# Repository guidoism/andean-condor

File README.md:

# Andean Condor

48 key monoblock split keyboard

## Characteristics

- 3x6 core + 6 key thumb cluster per hand
- Pro-micro MCU footprint (note: it's right-side-up which apparently goes against the current trend)
- Nice!View headers (untested)

## Inspiration 

- Kyria -- A huge inpsiration, the thumb cluster in particular is taken directly from the Kyria
- Absolem -- Monoblock split and angles taken from Absolem

## Changes in version 3

- Move diodes to sit next to their switches to save space and use SMT to reduce size and holes
- Move reset switch away from usb plug
- Move Nice!View to its standard location just below the Nice!Nano
- Screw holes for MCU plate cover and seperate MCU plate cover with optional place for Nice!View
- Second PCB attached to top PCB to hide pointy through hole component stuff
- Holes in the PCB in a few places for magnets to hole keyboard inside case without screws
- Place to attach larger battery so it's not flopping around
- Place to connect battery to PCB rather than directly to Nice!Nano
- Place for 8x1 neopixels to indicate stuff? Maybe on plate cover?
- Place 7-segment display? Maybe on plate cover?
- Maybe plate cover has legs to break out pins?

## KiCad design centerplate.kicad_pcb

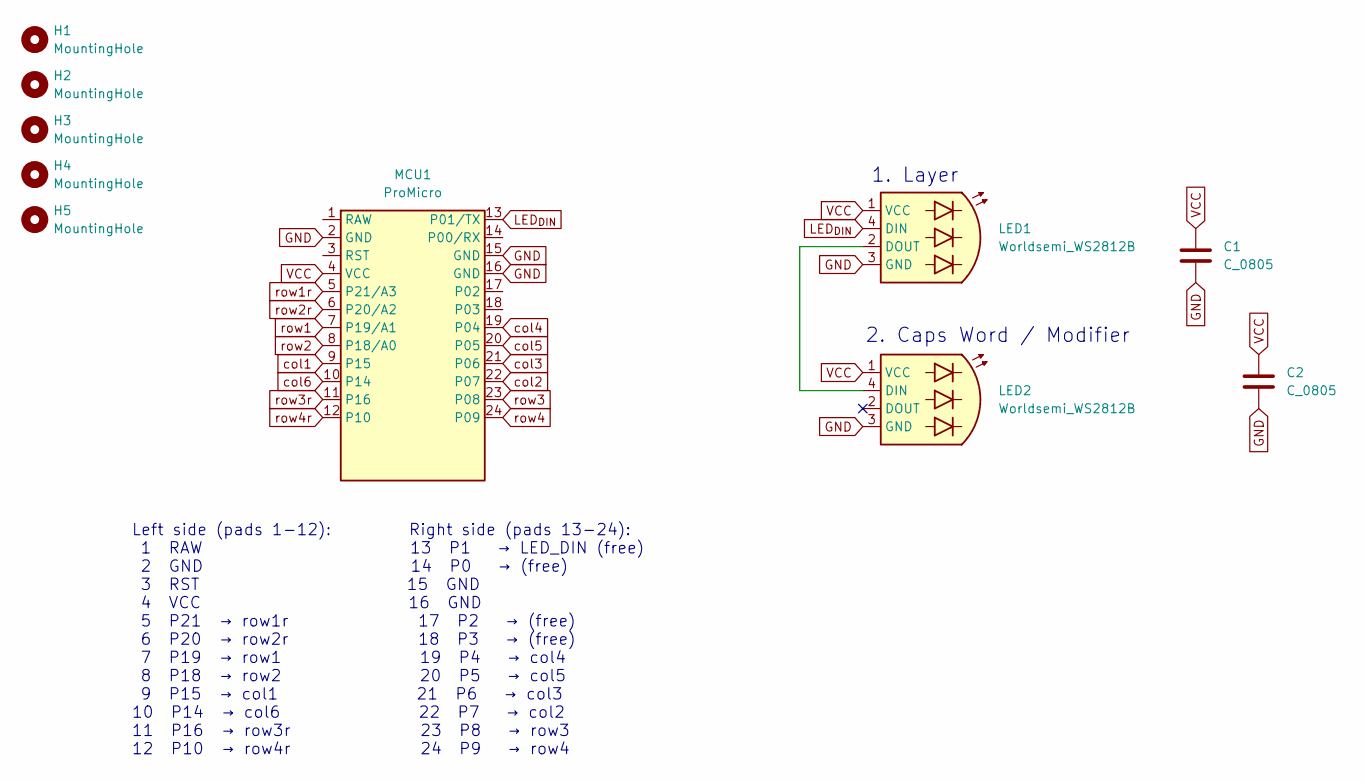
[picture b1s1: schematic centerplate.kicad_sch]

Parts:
C1, C2: C_0805; C_0805_2012Metric
H1, H2, H3, H4, H5: MountingHole; M2_HOLE_v3
LED1, LED2: Worldsemi_WS2812B; LED_WS2812B_PLCC4_5.0x5.0mm_P3.2mm
MCU1: ProMicro

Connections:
GND: C1.2, C2.2, LED1.3 (GND), LED2.3 (GND), MCU1.2 (GND), MCU1.15 (GND), MCU1.16 (GND)
LED_{DIN}: LED1.4 (DIN), MCU1.13 (P01/TX)
unnamed: LED1.2 (DOUT), LED2.4 (DIN)
VCC: C1.1, C2.1, LED1.1 (VCC), LED2.1 (VCC), MCU1.4 (VCC)
col1: MCU1.9 (P15)
col2: MCU1.22 (P07)
col3: MCU1.21 (P06)
col4: MCU1.19 (P04)
col5: MCU1.20 (P05)
col6: MCU1.10 (P14)
row1: MCU1.7 (P19/A1)
row1r: MCU1.5 (P21/A3)
row2: MCU1.8 (P18/A0)
row2r: MCU1.6 (P20/A2)
row3: MCU1.23 (P08)
row3r: MCU1.11 (P16)
row4: MCU1.24 (P09)
row4r: MCU1.12 (P10)

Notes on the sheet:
Left side (pads 1-12): Right side (pads 13-24): 1 RAW 13 P1 → LED_DIN (free) 2 GND 14 P0 → (free) 3 RST 15 GND 4 VCC 16 GND 5 P21 → row1r 17 P2 → (free) 6 P20 → row2r 18 P3 → (free) 7 P19 → row1 19 P4 → col4 8 P18 → row2 20 P5 → col5 9 P15 → col1 21 P6 → col3 10 P14 → col6 22 P7 → col2 11 P16 → row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
2. Caps Word / Modifier
1. Layer

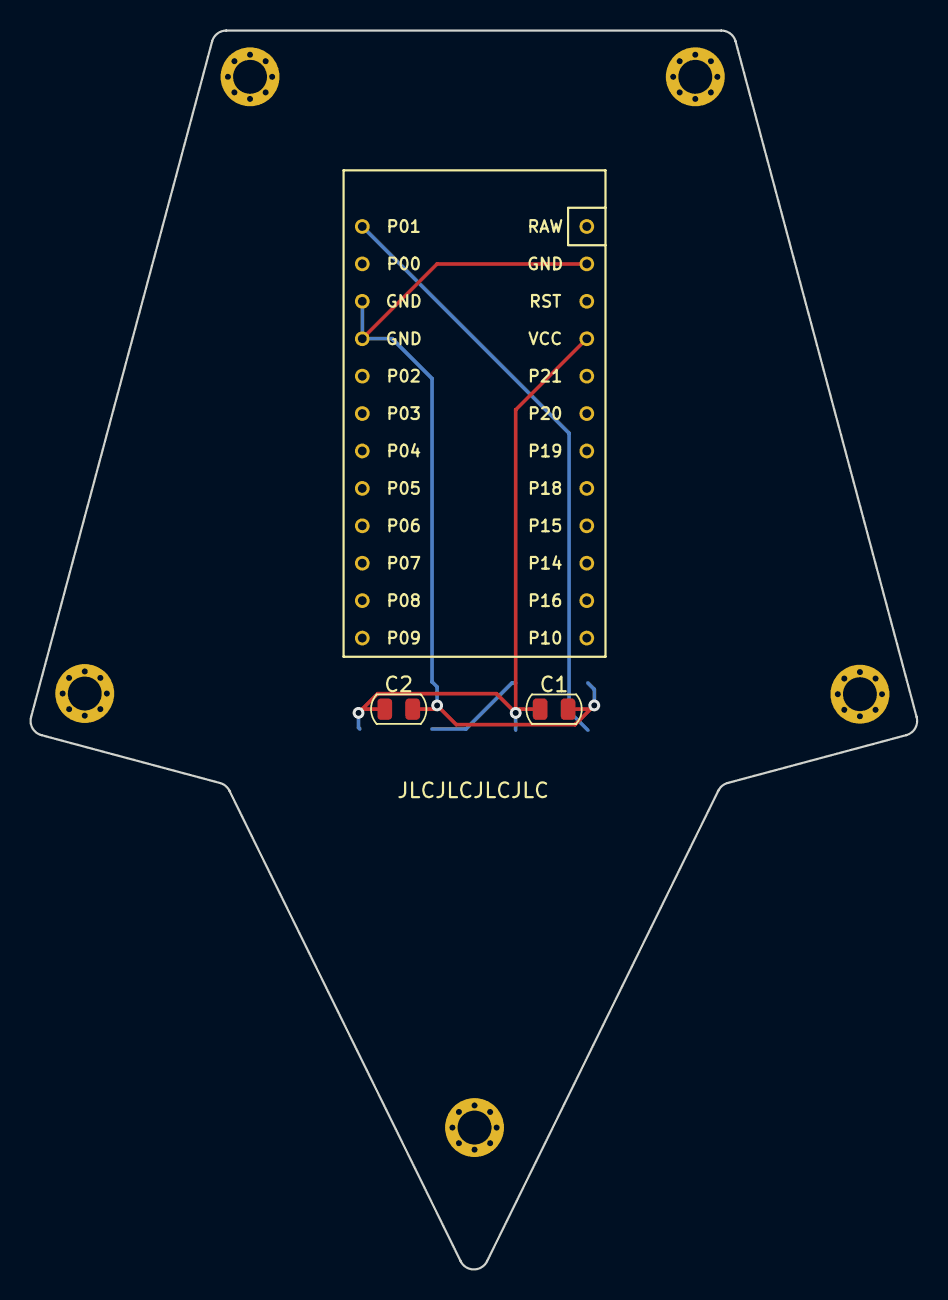
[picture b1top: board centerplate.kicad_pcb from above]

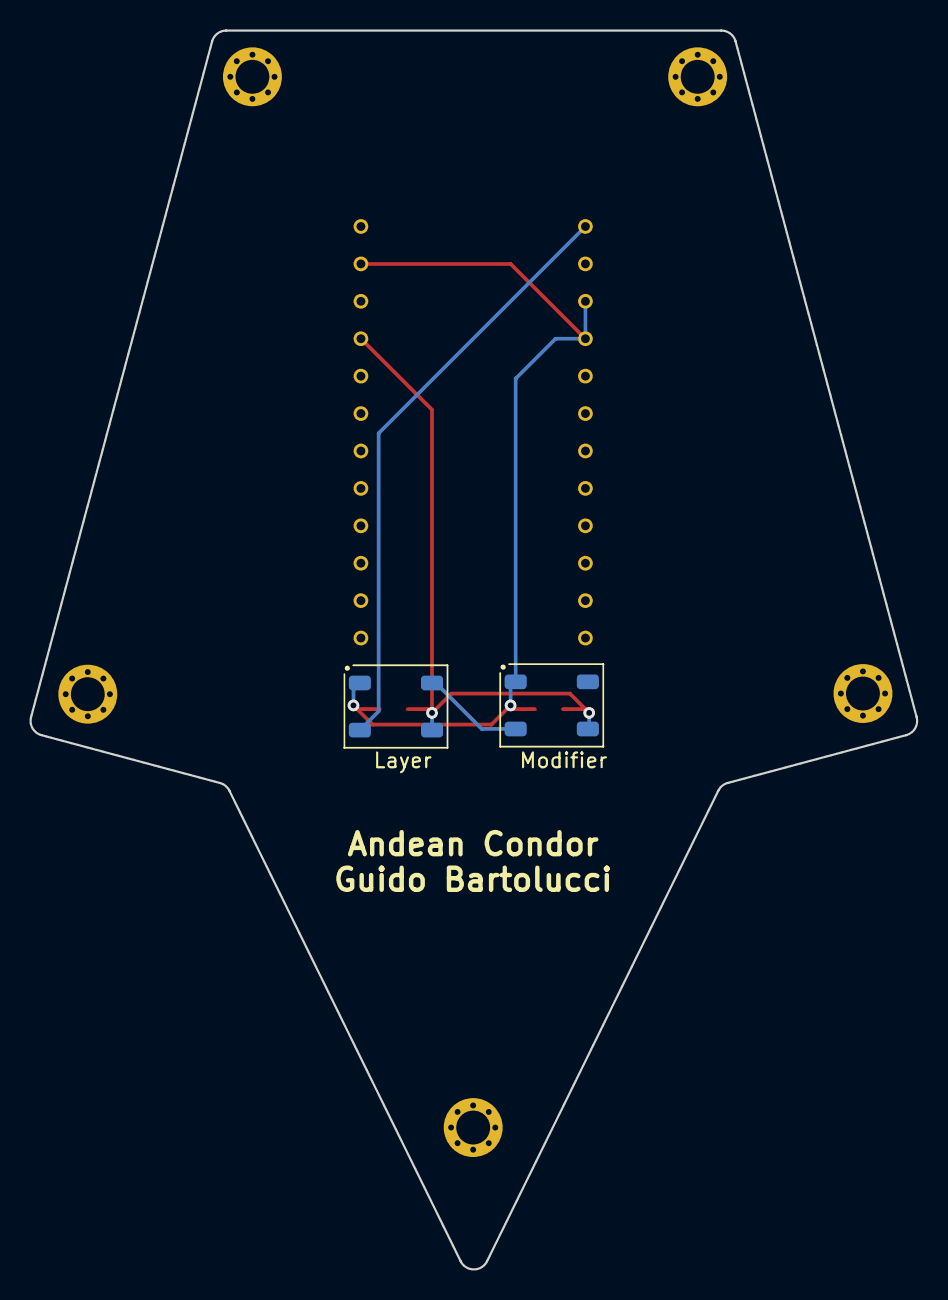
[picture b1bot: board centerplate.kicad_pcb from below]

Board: 2 copper layers, 60.2 x 84.1 mm, 10 parts (2 on the bottom side), 4 nets.

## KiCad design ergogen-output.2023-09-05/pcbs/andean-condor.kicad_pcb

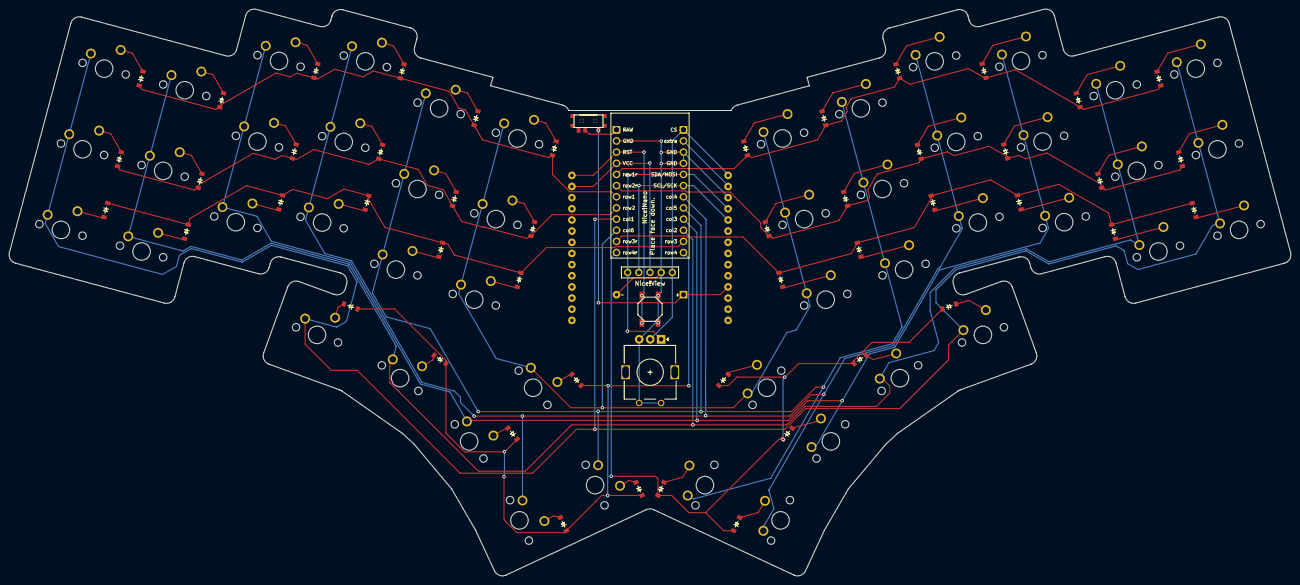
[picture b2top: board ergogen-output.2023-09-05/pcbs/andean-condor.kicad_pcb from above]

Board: 2 copper layers, 291.8 x 129.0 mm, 101 parts (0 on the bottom side), 69 nets.

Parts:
B1: SW_TACT_ALPS_SKQGABE010
D1, D2, D3, D4, D5, D6, D7, D8, D9, D10, D11, D12, D13, D14, D15, D16, D17, D18, D19, D20, D21, D22, D23, D24, D25, D26, D27, D28, D29, D30, D31, D32, D33, D34, D35, D36, D37, D38, D39, D40, D41, D42, D43, D44, D45, D46, D47, D48: ComboDiode
MCU1: ProMicro
Nice!View1: niceview_headers
ROT1: rotary_encoder
S1, S2, S3, S4, S5, S6, S7, S8, S9, S10, S11, S12, S13, S14, S15, S16, S17, S18, S19, S20, S21, S22, S23, S24, S25, S26, S27, S28, S29, S30, S31, S32, S33, S34, S35, S36, S37, S38, S39, S40, S41, S42, S43, S44, S45, S46, S47, S48: MX
T1: SPDT_C128955

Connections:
CS: MCU1.13, Nice!View1.1, ROT1.C
GND: B1.1, MCU1.2, MCU1.15, MCU1.16, Nice!View1.1, ROT1.1, ROT1.2, ROT1.B
RAW: MCU1.1, T1.2
RST: B1.2, MCU1.3
SCL: MCU1.18, Nice!View1.3
SDA: MCU1.17, Nice!View1.4, ROT1.A
VCC: MCU1.4, Nice!View1.2
col1: MCU1.9, S1.2, S2.2, S3.2, S19.2, S25.2, S26.2, S27.2, S43.2
col2: MCU1.22, S4.2, S5.2, S6.2, S20.2, S28.2, S29.2, S30.2, S44.2
col3: MCU1.21, S7.2, S8.2, S9.2, S21.2, S31.2, S32.2, S33.2, S45.2
col4: MCU1.19, S10.2, S11.2, S12.2, S23.2, S34.2, S35.2, S36.2, S47.2
col5: MCU1.20, S13.2, S14.2, S15.2, S24.2, S37.2, S38.2, S39.2, S48.2
col6: MCU1.10, S16.2, S17.2, S18.2, S22.2, S40.2, S41.2, S42.2, S46.2
far_thumb: D41.2, S23.1
far_top: D42.2, S24.1
farpinky_bottom: D13.2, S1.1
farpinky_home: D1.2, S2.1
farpinky_top: D2.2, S3.1
home_thumb: D39.2, S21.1
home_top: D40.2, S22.1
index_bottom: D17.2, S13.1
index_home: D9.2, S14.1
index_top: D10.2, S15.1
inner_bottom: D18.2, S16.1
inner_home: D11.2, S17.1
inner_top: D12.2, S18.1
middle_bottom: D16.2, S10.1
middle_home: D7.2, S11.1
middle_top: D8.2, S12.1
mirror_far_thumb: D47.2, S47.1
mirror_far_top: D48.2, S48.1
mirror_farpinky_bottom: D31.2, S25.1
mirror_farpinky_home: D19.2, S26.1
mirror_farpinky_top: D20.2, S27.1
mirror_home_thumb: D45.2, S45.1
mirror_home_top: D46.2, S46.1
mirror_index_bottom: D35.2, S37.1
mirror_index_home: D27.2, S38.1
mirror_index_top: D28.2, S39.1
mirror_inner_bottom: D36.2, S40.1
mirror_inner_home: D29.2, S41.1
mirror_inner_top: D30.2, S42.1
mirror_middle_bottom: D34.2, S34.1
mirror_middle_home: D25.2, S35.1
mirror_middle_top: D26.2, S36.1
mirror_near_thumb: D44.2, S44.1
mirror_pinky_bottom: D32.2, S28.1
mirror_pinky_home: D21.2, S29.1
mirror_pinky_top: D22.2, S30.1
mirror_ring_bottom: D33.2, S31.1
mirror_ring_home: D23.2, S32.1
mirror_ring_top: D24.2, S33.1
mirror_tucky_thumb: D43.2, S43.1
near_thumb: D38.2, S20.1
pinky_bottom: D14.2, S4.1
pinky_home: D3.2, S5.1
pinky_top: D4.2, S6.1
ring_bottom: D15.2, S7.1
ring_home: D5.2, S8.1
ring_top: D6.2, S9.1
row1: D2.1, D4.1, D6.1, D8.1, D10.1, D12.1, MCU1.7
row1r: D20.1, D22.1, D24.1, D26.1, D28.1, D30.1, MCU1.5
row2: D1.1, D3.1, D5.1, D7.1, D9.1, D11.1, MCU1.8
row2r: D19.1, D21.1, D23.1, D25.1, D27.1, D29.1, MCU1.6
row3: D13.1, D14.1, D15.1, D16.1, D17.1, D18.1, MCU1.23
row3r: D31.1, D32.1, D33.1, D34.1, D35.1, D36.1, MCU1.11
row4: D37.1, D38.1, D39.1, D40.1, D41.1, D42.1, MCU1.24
row4r: D43.1, D44.1, D45.1, D46.1, D47.1, D48.1, MCU1.12
tucky_thumb: D37.2, S19.1

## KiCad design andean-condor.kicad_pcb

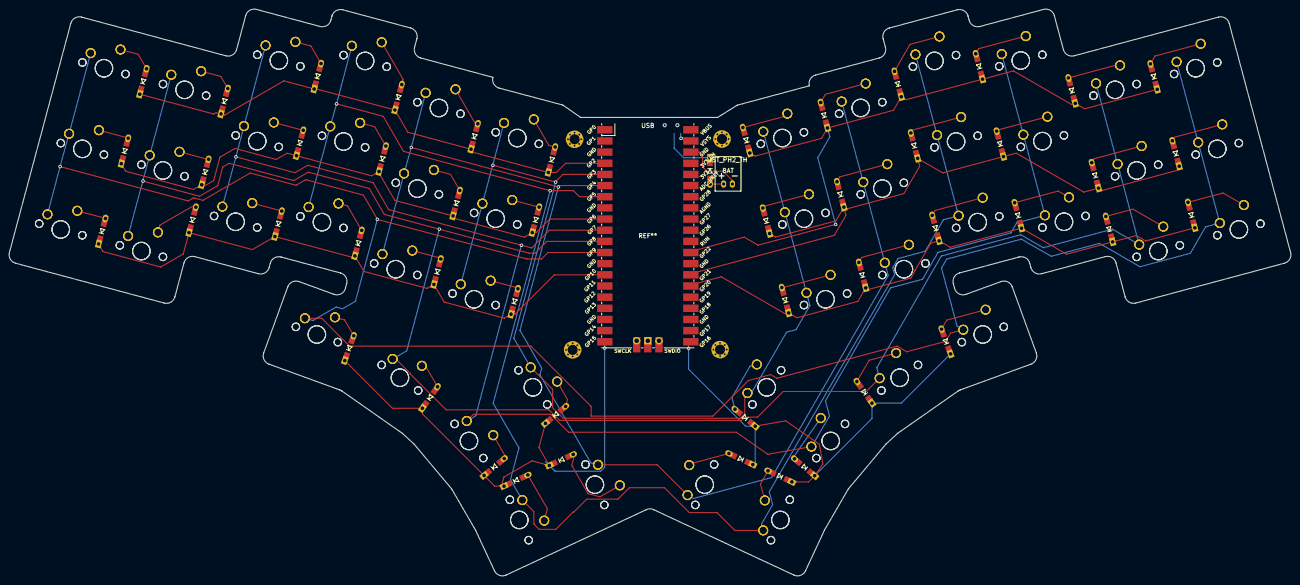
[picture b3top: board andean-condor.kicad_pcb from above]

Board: 2 copper layers, 291.8 x 129.0 mm, 151 parts (1 on the bottom side), 62 nets.

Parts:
D33, D33#2, D33#3, D34, D34#2, D35, D35#2, D36, D36#2, D37, D37#2, D38, D38#2, D39, D39#2, D40, D40#2, D41, D41#2, D42, D42#2, D43, D43#2, D44, D44#2, D45, D45#2, D46, D46#2, D47, D47#2, D48, D48#2, D49, D49#2, D50, D50#2, D51, D51#2, D52, D52#2, D53, D54, D55, D56, D57, D58, D59, D60: D; D3_TH_SMD_v2
JST_PH2_TH: BAT; JST_PH2_TH
Ref**: Val**; M2_HOLE_v3
Ref**#2, Ref**#3, Ref**#4: Val**; M2_HOLE_v3
S1, S2, S3, S4, S5, S6, S7, S8, S9, S10, S11, S12, S13, S14, S15, S16, S17, S18, S19, S20, S21, S22, S23, S24, S25, S26, S27, S28, S29, S30, S31, S32, S33, S34, S35, S36, S37, S38, S39, S40, S41, S42, S43, S44, S45, S46, S47, S48, S49, S50, S51, S52, S53, S54, S55, S56, S57, S58, S59, S60, S61, S62, S63, S64, S65, S66, S67, S68, S69, S70, S71, S72, S73, S74, S75, S76, S77, S78, S79, S80, S81, S82, S83, S84, S85, S86, S87, S88, S89, S90, S91, S92, S93, S94, S95, S96: MX
SW1: PWR; switch-MSK-12C02-smd

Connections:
col1: S1.2, S2.2, S3.2, S19.2, S25.2, S26.2, S27.2, S43.2, S49.2, S50.2, S51.2, S67.2, S73.2, S74.2, S75.2, S91.2
col2: S4.2, S5.2, S6.2, S20.2, S28.2, S29.2, S30.2, S44.2, S52.2, S53.2, S54.2, S68.2, S76.2, S77.2, S78.2, S92.2
col3: S7.2, S8.2, S9.2, S21.2, S31.2, S32.2, S33.2, S45.2, S55.2, S56.2, S57.2, S69.2, S79.2, S80.2, S81.2, S93.2
col4: S10.2, S11.2, S12.2, S23.2, S34.2, S35.2, S36.2, S47.2, S58.2, S59.2, S60.2, S71.2, S82.2, S83.2, S84.2, S95.2
col5: S13.2, S14.2, S15.2, S24.2, S37.2, S38.2, S39.2, S48.2, S61.2, S62.2, S63.2, S72.2, S85.2, S86.2, S87.2, S96.2
col6: S16.2, S17.2, S18.2, S22.2, S40.2, S41.2, S42.2, S46.2, S64.2, S65.2, S66.2, S70.2, S88.2, S89.2, S90.2, S94.2
far_thumb: D55.2, S23.1, S95.1
far_top: D56.2, S24.1, S96.1
farpinky_bottom: D49.2, S1.1, S73.1
farpinky_home: D44#2.2, S2.1, S74.1
farpinky_top: D37#2.2, S3.1, S75.1
home_thumb: D53.2, S21.1, S93.1
home_top: D54.2, S22.1, S94.1
index_bottom: D47.2, S13.1, S85.1
index_home: D40#2.2, S14.1, S86.1
index_top: D34#2.2, S15.1, S87.1
inner_bottom: D48.2, S16.1, S88.1
inner_home: D41#2.2, S17.1, S89.1
inner_top: D35.2, S18.1, S90.1
middle_bottom: D46.2, S10.1, S82.1
middle_home: D39#2.2, S11.1, S83.1
middle_top: D33#3.2, S12.1, S84.1
mirror_far_thumb: D50.2, S47.1, S71.1
mirror_far_top: D49#2.2, S48.1, S72.1
mirror_farpinky_bottom: D60.2, S25.1, S49.1
mirror_farpinky_home: D42.2, S26.1, S50.1
mirror_farpinky_top: D40.2, S27.1, S51.1
mirror_home_thumb: D52#2.2, S45.1, S69.1
mirror_home_top: D51.2, S46.1, S70.1
mirror_index_bottom: D46#2.2, S37.1, S61.1
mirror_index_home: D37.2, S38.1, S62.1
mirror_index_top: D35#2.2, S39.1, S63.1
mirror_inner_bottom: D45#2.2, S40.1, S64.1
mirror_inner_home: D44.2, S41.1, S65.1
mirror_inner_top: D34.2, S42.1, S66.1
mirror_middle_bottom: D47#2.2, S34.1, S58.1
mirror_middle_home: D38.2, S35.1, S59.1
mirror_middle_top: D36.2, S36.1, S60.1
mirror_near_thumb: D57.2, S44.1, S68.1
mirror_pinky_bottom: D59.2, S28.1, S52.1
mirror_pinky_home: D41.2, S29.1, S53.1
mirror_pinky_top: D39.2, S30.1, S54.1
mirror_ring_bottom: D48#2.2, S31.1, S55.1
mirror_ring_home: D43#2.2, S32.1, S56.1
mirror_ring_top: D33.2, S33.1, S57.1
mirror_tucky_thumb: D58.2, S43.1, S67.1
near_thumb: D52.2, S20.1, S92.1
pinky_bottom: D50#2.2, S4.1, S76.1
pinky_home: D43.2, S5.1, S77.1
pinky_top: D38#2.2, S6.1, S78.1
ring_bottom: D45.2, S7.1, S79.1
ring_home: D42#2.2, S8.1, S80.1
ring_top: D36#2.2, S9.1, S81.1
row1: D33#3.1, D34#2.1, D35.1, D36#2.1, D37#2.1, D38#2.1
row1r: D33.1, D34.1, D35#2.1, D36.1, D39.1, D40.1
row2: D39#2.1, D40#2.1, D41#2.1, D42#2.1, D43.1, D44#2.1
row2r: D37.1, D38.1, D41.1, D42.1, D43#2.1, D44.1
row3: D45.1, D46.1, D47.1, D48.1, D49.1, D50#2.1
row3r: D45#2.1, D46#2.1, D47#2.1, D48#2.1, D59.1, D60.1
row4: D51#2.1, D52.1, D53.1, D54.1, D55.1, D56.1
row4r: D49#2.1, D50.1, D51.1, D52#2.1, D57.1, D58.1
tucky_thumb: D51#2.2, S19.1, S91.1

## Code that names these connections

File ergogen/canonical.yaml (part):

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    autobind: 10
    skip: false
    asym: both
    colrow: farpinky_bottom
    name: matrix_farpinky_bottom
    column_net: col1
    row_net: row3
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    autobind: 10
    skip: false
    asym: both
    colrow: farpinky_home
    name: matrix_farpinky_home
    column_net: col1
    row_net: row2
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    autobind: 10
    skip: false
    asym: both
    colrow: farpinky_top
    name: matrix_farpinky_top
    column_net: col1
    row_net: row1
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    autobind: 10
    skip: false
    asym: both
    colrow: pinky_bottom
    name: matrix_pinky_bottom
    column_net: col2
    row_net: row3
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    autobind: 10
    skip: false
    asym: both
    colrow: pinky_home
    name: matrix_pinky_home
    column_net: col2
    row_net: row2
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    autobind: 10
    skip: false
    asym: both
    colrow: pinky_top
    name: matrix_pinky_top
    column_net: col2
    row_net: row1
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    autobind: 10
    skip: false
    asym: both
    colrow: mirror_farpinky_bottom
    name: mirror_matrix_farpinky_bottom
    column_net: col1
    row_net: row3
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    autobind: 10
    skip: false
    asym: both
    colrow: mirror_farpinky_home
    name: mirror_matrix_farpinky_home
    column_net: col1
    row_net: row2
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    autobind: 10
    skip: false
    asym: both
    colrow: mirror_farpinky_top
    name: mirror_matrix_farpinky_top
    column_net: col1
    row_net: row1
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    autobind: 10
    skip: false
    asym: both
    colrow: mirror_pinky_bottom
    name: mirror_matrix_pinky_bottom
    column_net: col2
    row_net: row3
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    autobind: 10
    skip: false
    asym: both
    colrow: mirror_pinky_home
    name: mirror_matrix_pinky_home
    column_net: col2
    row_net: row2
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    autobind: 10
    skip: false
    asym: both
    colrow: mirror_pinky_top
    name: mirror_matrix_pinky_top
    column_net: col2
    row_net: row1
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
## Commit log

2023-01-19 Inital commit of the files
2023-01-19 Added some text to the pcb
2023-01-19 Add pic of pcb
2023-01-19 Checkpoint
2023-06-02 Added Pico W version
2023-09-01 Added readme back
2023-09-01 Start of a v3
2024-12-10 Created outline for switchplate
2024-12-10 Fix update to thumbfan outline
2024-12-10 Added place to put mounting holes on the top sides
2024-12-10 Added the second set of mounting additions to the top
2024-12-10 Added mounting holes to the top
2024-12-10 Changed switch plate to be more regular shaped
2024-12-10 Added screw holes
2024-12-10 Added bottom plate
2024-12-11 Added cutout for mcu to be accessed
    This is in order to reboot it or remove it... hopefully
2024-12-11 Increase size of mcu cutout
2024-12-11 Added switch plate to pcbs
2024-12-13 Added outline for key locations
2024-12-13 Added pcb demo
2026-03-17 Add mxkeyoutlines and center_top_plate definitions
2026-03-20 Added centerpiece pcb
